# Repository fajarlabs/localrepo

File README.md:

# localrepo
Temporary Project Repository

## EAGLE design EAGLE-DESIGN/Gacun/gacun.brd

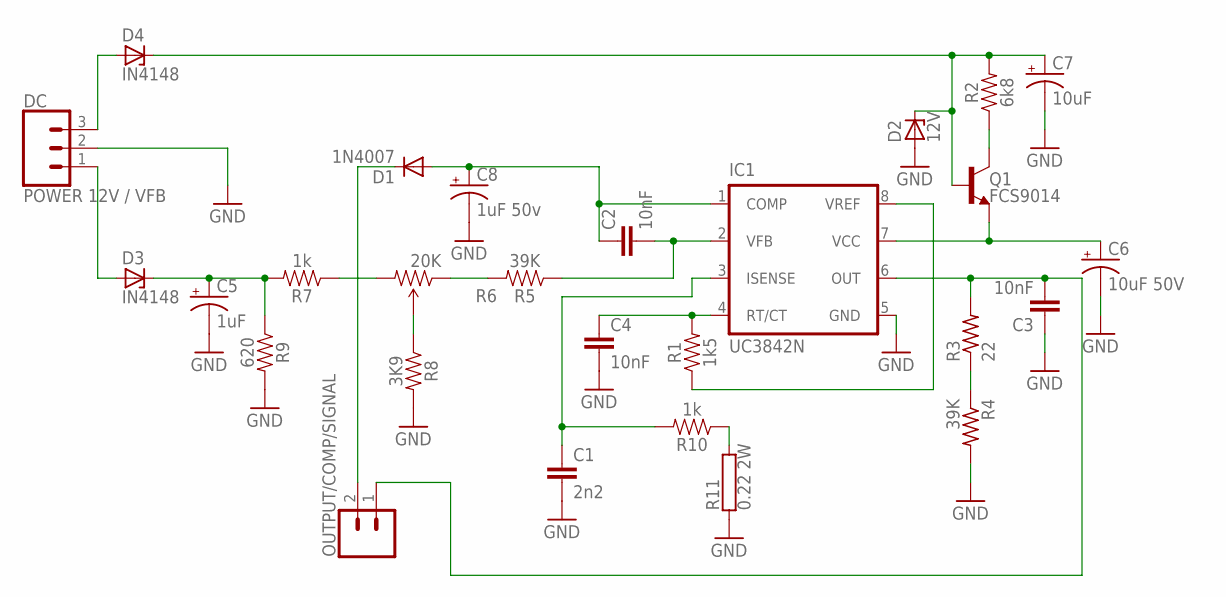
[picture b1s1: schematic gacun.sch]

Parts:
C1: 2n2; CAP-PTH-10MM
C2, C3, C4: 10nF; CAP-PTH-10MM
C5: 1uF; CPOL-RADIAL-2.5MM-5MM
C6: 10uF 50V; E2-4
C7: 10uF; CPOL-RADIAL-2.5MM-5MM
C8: 1uF 50v; CPOL-RADIAL-2.5MM-5MM
D1: 1N4007; DO41-10
D2: 12V; ZDIO-7.5
D3, D4: IN4148; ZDIO-7.5
DC: POWER 12V / VFB; 1X03
IC1: UC3842N; DIL08
OUTPUT/COMP/SIGNAL: CONN_02; 1X02
Q1: FCS9014; TO-92-EZ
R1: 1k5; AXIAL-0.3
R2: 6k8; AXIAL-0.3
R3: 22; 0204/7
R4: 39K; 0204/7
R5: 39K; AXIAL-0.3
R6: 20K; TRIM_POT_PTH
R7, R10: 1k; AXIAL-0.3
R8: 3K9; AXIAL-0.3
R9: 620; AXIAL-0.3
R11: 0.22 2W; KH206-8

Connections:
GND: C1.2, C3.1, C4.2, C5.2 (-), C6.-, C7.2 (-), C8.2 (-), D2.A, DC.2, IC1.5 (GND), R4.2, R8.P$2 (2), R9.P$2 (2), R11.1
unnamed: C2.1, C8.1 (+), D1.A, IC1.1 (COMP)
unnamed: C2.2, IC1.2 (VFB), R5.P$1 (1)
unnamed: C4.1, IC1.4 (RT/CT), R1.P$2 (2)
unnamed: C3.2, IC1.6 (OUT), OUTPUT/COMP/SIGNAL.1, R3.2
unnamed: C6.+, IC1.7 (VCC), Q1.1 (E)
unnamed: Q1.3 (C), R2.P$1 (1)
unnamed: C7.1 (+), D2.C, D4.C, Q1.2 (B), R2.P$2 (2)
unnamed: R3.1, R4.1
unnamed: IC1.8 (VREF), R1.P$1 (1)
unnamed: R5.P$2 (2), R6.1 (CCW)
unnamed: R6.3 (CW), R7.P$1 (1)
unnamed: R6.2 (WIPER), R8.P$1 (1)
unnamed: C5.1 (+), D3.C, R7.P$2 (2), R9.P$1 (1)
unnamed: D1.C, OUTPUT/COMP/SIGNAL.2
unnamed: C1.1, IC1.3 (ISENSE), R10.P$2 (2)
unnamed: D3.A, DC.1
unnamed: D4.A, DC.3
unnamed: R10.P$1 (1), R11.2

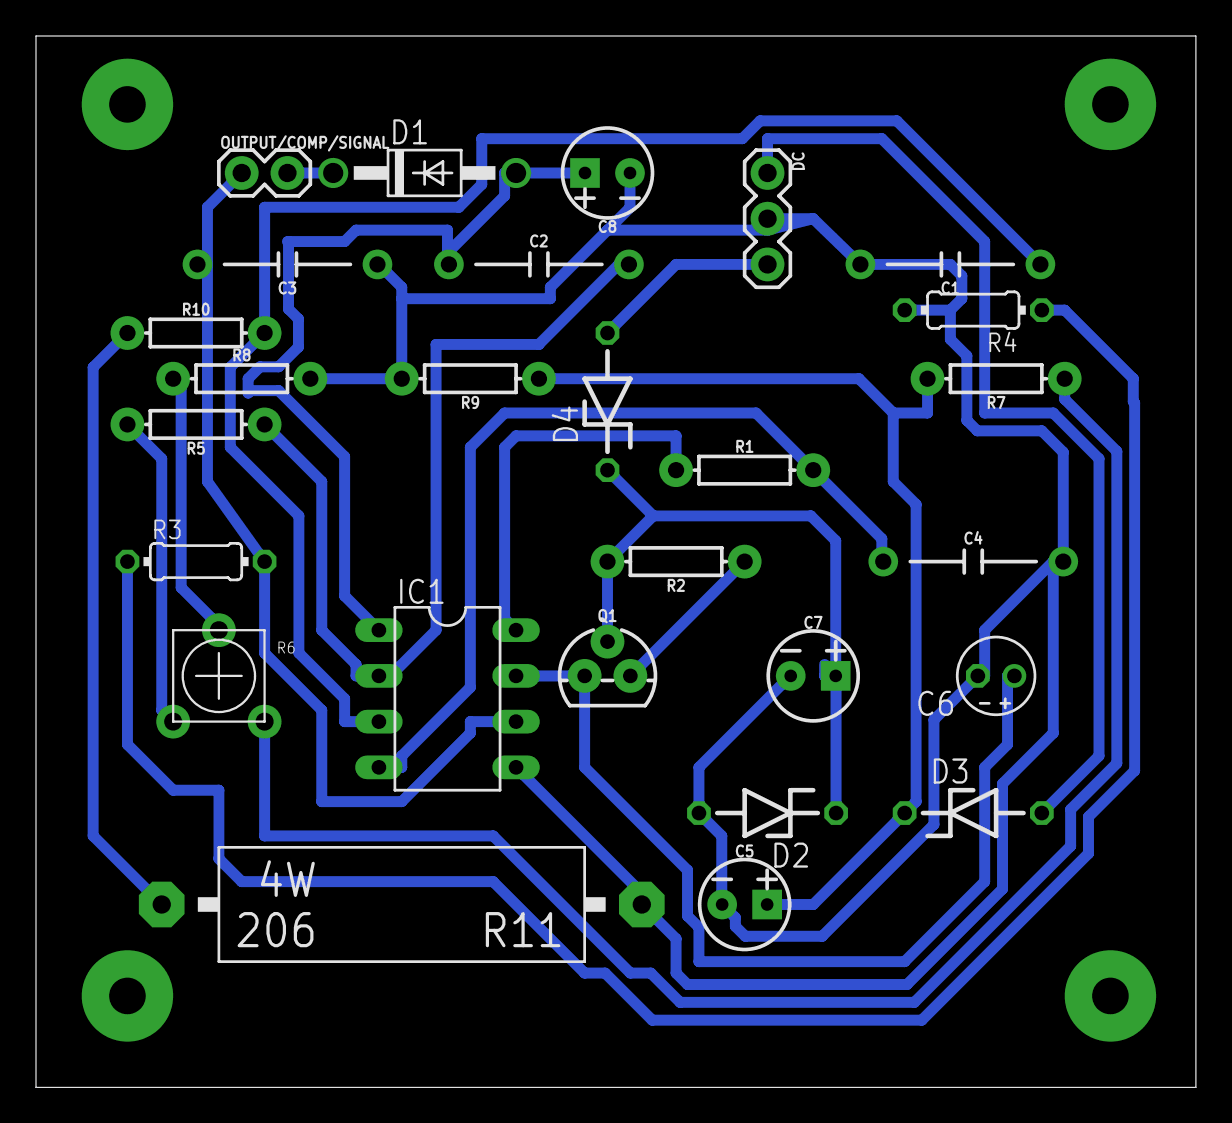
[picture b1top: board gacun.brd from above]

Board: 2 copper layers, 64.4 x 58.4 mm, 27 parts (0 on the bottom side), 19 nets.

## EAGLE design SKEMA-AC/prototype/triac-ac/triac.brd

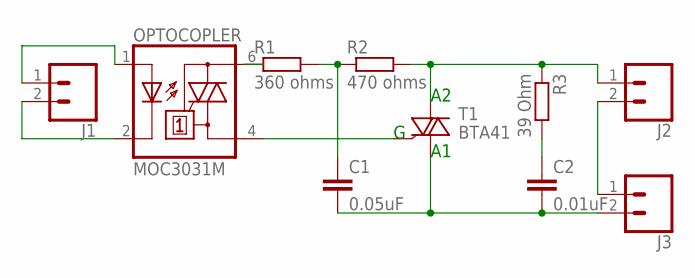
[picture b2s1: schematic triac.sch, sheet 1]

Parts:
C1: 0.05uF; C7.5B3
C2: 0.01uF; C7.5B3
J1, J2, J3: CONN_02JST-PTH-2; JST-2-PTH
OPTOCOPLER: MOC3031M; DIL06
R1: 360 ohms; 0204/5
R2: 470 ohms; 0204/5
R3: 39 Ohm; 0204/5
T1: BTA41; TO220BV

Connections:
unnamed: J1.2, OPTOCOPLER.2 (C)
unnamed: J1.1, OPTOCOPLER.1 (A)
unnamed: OPTOCOPLER.6 (A2), R1.1
unnamed: C1.1, R1.2, R2.1
unnamed: C1.2, C2.2, J3.2, T1.T1 (A1)
unnamed: OPTOCOPLER.4 (A1), T1.G
unnamed: J2.1, R2.2, R3.1, T1.T2 (A2)
unnamed: C2.1, R3.2
unnamed: J2.2, J3.1

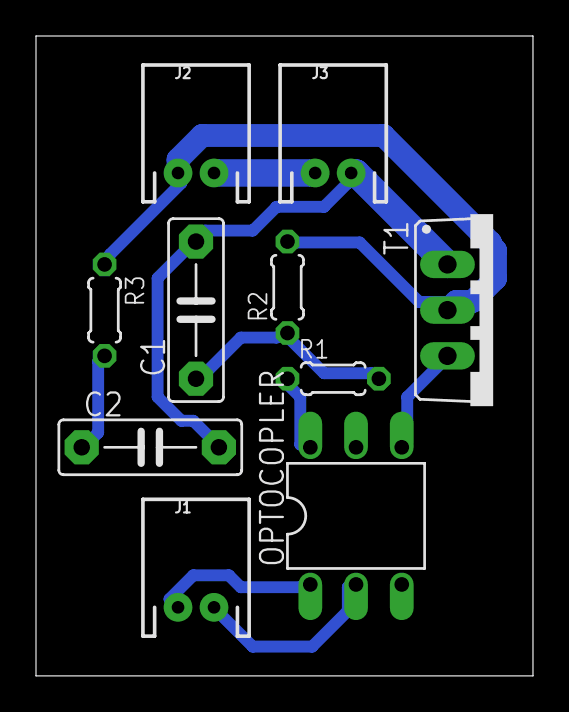
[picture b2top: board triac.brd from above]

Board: 2 copper layers, 27.6 x 35.5 mm, 10 parts (0 on the bottom side), 9 nets.

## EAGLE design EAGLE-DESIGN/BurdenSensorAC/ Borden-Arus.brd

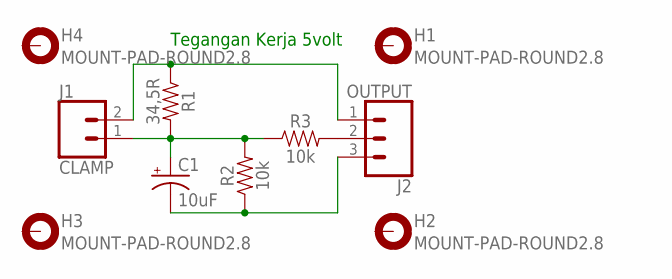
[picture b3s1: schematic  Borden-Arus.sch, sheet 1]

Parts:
C1: 10uF; CPOL-RADIAL-2.5MM-5MM
H1, H2, H3, H4: MOUNT-PAD-ROUND2.8; 2,8-PAD
J1: CLAMP; 1X02
J2: OUTPUT; 1X03
R1: 34,5R; AXIAL-0.3
R2, R3: 10k; AXIAL-0.3

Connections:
unnamed: J2.2, R3.P$2 (2)
unnamed: J1.2, J2.1, R1.P$1 (1)
unnamed: C1.1 (+), J1.1, R1.P$2 (2), R2.P$2 (2), R3.P$1 (1)
unnamed: C1.2 (-), J2.3, R2.P$1 (1)

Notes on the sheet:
Tegangan Kerja 5volt

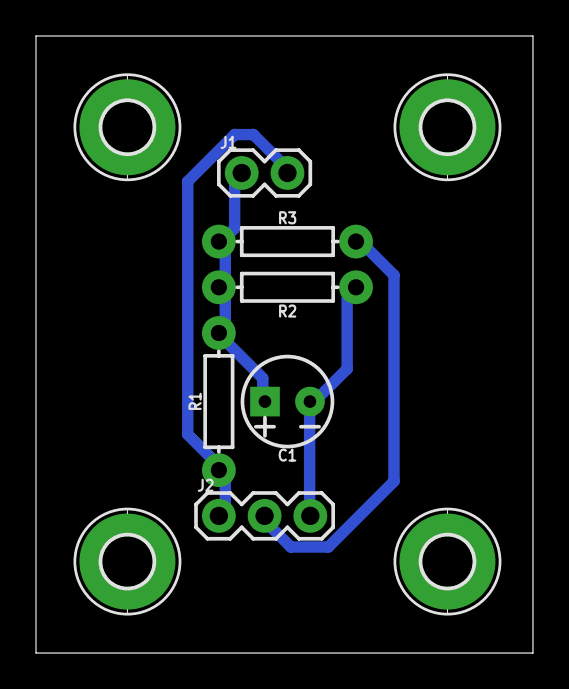
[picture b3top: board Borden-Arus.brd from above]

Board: 2 copper layers, 27.6 x 34.3 mm, 10 parts (0 on the bottom side), 4 nets.

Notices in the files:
parts and their libraries:
SparkFun-Capacitors: Licensing: Creative Commons ShareAlike 4.0 International - https://creativecommons.org/licenses/by-sa/4.0
